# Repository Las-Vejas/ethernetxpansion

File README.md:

# ethernetxpansion

This is an ethernet adapter for the [Hackxpansion console](https://github.com/hackclub/hackxpansion). It uses the WIZnet W5500 chip and the Hanrun HR911105A ethernet plug.

<h2 align="center">Pictures</h2>

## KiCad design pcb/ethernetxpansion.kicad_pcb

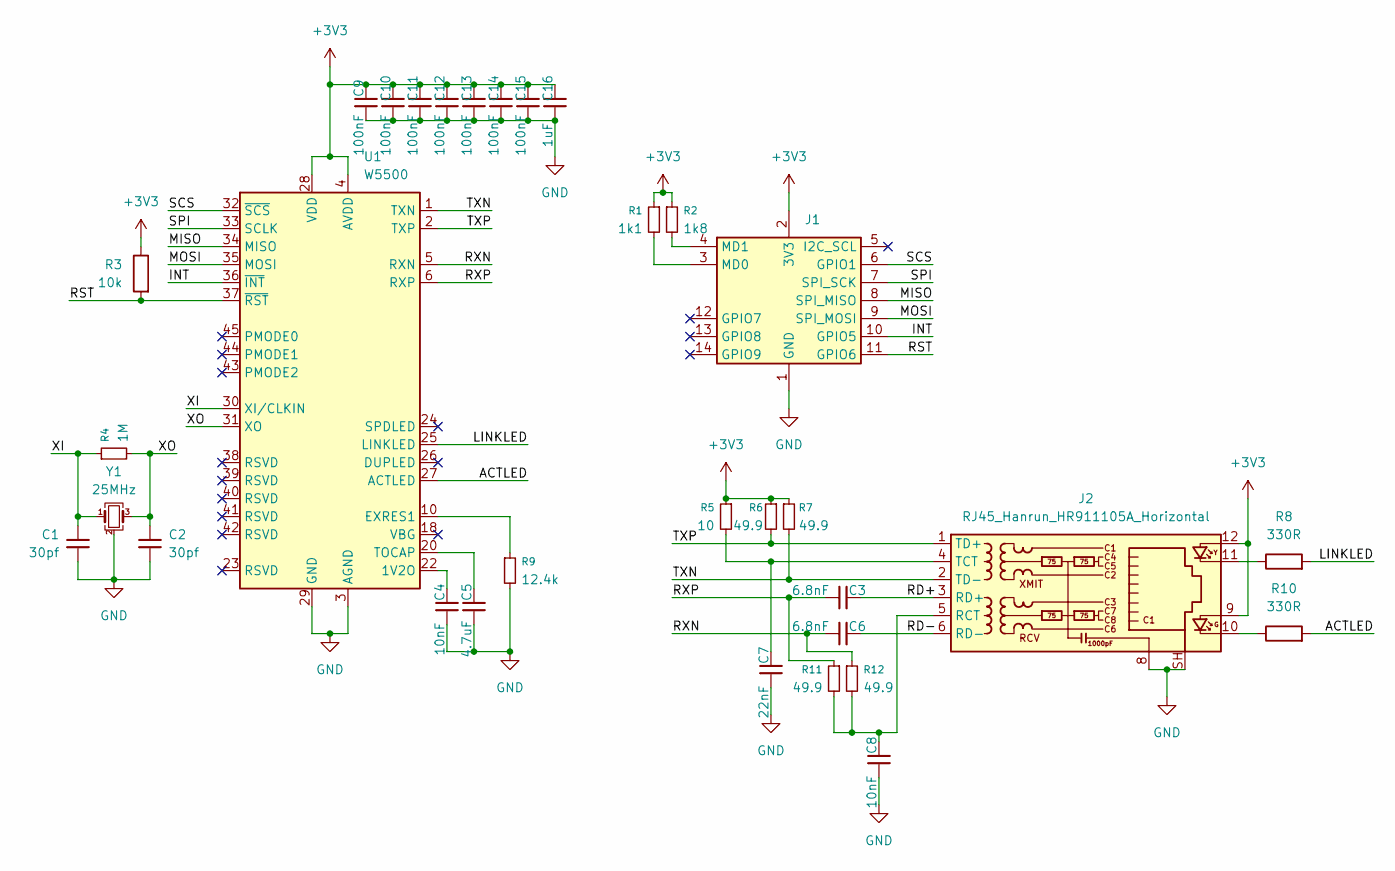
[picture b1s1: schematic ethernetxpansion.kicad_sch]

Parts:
C1, C2: 30pf; C_0402_1005Metric
C3, C6: 6.8nF; C_0402_1005Metric
C4, C8: 10nF; C_0402_1005Metric
C5: 4.7uF; C_0402_1005Metric
C7: 22nF; C_0402_1005Metric
C9, C10, C11, C12, C13, C14, C15: 100nF; C_0402_1005Metric
C16: 1uF; C_0402_1005Metric
J1: Male_Module
J2: RJ45_Hanrun_HR911105A_Horizontal
R1: 1k1; R_0402_1005Metric
R2: 1k8; R_0402_1005Metric
R3: 10k; R_0402_1005Metric
R4: 1M; R_0402_1005Metric
R5: 10; R_0402_1005Metric
R6, R7, R11, R12: 49.9; R_0402_1005Metric
R8, R10: 330R; R_0402_1005Metric
R9: 12.4k; R_0402_1005Metric
U1: W5500; LQFP-48_7x7mm_P0.5mm
Y1: 25MHz; Crystal_SMD_3225-4Pin_3.2x2.5mm

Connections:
+3V3: C9.2, C10.2, C11.2, C12.2, C13.2, C14.2, C15.2, C16.2, J1.2 (3V3), J2.9, J2.12, R1.1, R2.1, R3.1, R5.1, R6.1, R7.1, U1.4 (AVDD), U1.8 (AVDD), U1.11 (AVDD), U1.15 (AVDD), U1.17 (AVDD), U1.21 (AVDD), U1.28 (VDD)
/ACTLED: R10.2, U1.27 (ACTLED)
/INT: J1.10 (GPIO5), U1.36 (~INT)
/LINKLED: R8.2, U1.25 (LINKLED)
/MISO: J1.8 (SPI_MISO), U1.34 (MISO)
/MOSI: J1.9 (SPI_MOSI), U1.35 (MOSI)
/RD+: C3.2, J2.3 (RD+)
/RD-: C6.2, J2.6 (RD-)
/RST: J1.11 (GPIO6), R3.2, U1.37 (~RST)
/RXN: C6.1, R12.1, U1.5 (RXN)
/RXP: C3.1, R11.1, U1.6 (RXP)
/SCS: J1.6 (GPIO1), U1.32 (~SCS)
/SPI: J1.7 (SPI_SCK), U1.33 (SCLK)
/TXN: J2.2 (TD-), R7.2, U1.1 (TXN)
/TXP: J2.1 (TD+), R6.2, U1.2 (TXP)
/XI: C1.1, R4.1, U1.30 (XI/CLKIN), Y1.1
/XO: C2.1, R4.2, U1.31 (XO), Y1.3
GND: C1.2, C2.2, C4.1, C5.1, C7.1, C8.1, C9.1, C10.1, C11.1, C12.1, C13.1, C14.1, C15.1, C16.1, J1.1 (GND), J2.8, J2.SH, R9.2, U1.3 (AGND), U1.9 (AGND), U1.14 (AGND), U1.16 (AGND), U1.19 (AGND), U1.29 (GND), U1.48 (AGND), Y1.2 (G), Y1.4 (G)
unnamed: J1.3 (MD0), R1.2
unnamed: J1.4 (MD1), R2.2
unnamed: J2.10, R10.1
unnamed: J2.11, R8.1
unnamed: C8.2, J2.5 (RCT), R11.2, R12.2
unnamed: C7.2, J2.4 (TCT), R5.2
unnamed: C4.2, U1.22 (1V2O)
unnamed: R9.1, U1.10 (EXRES1)
unnamed: C5.2, U1.20 (TOCAP)

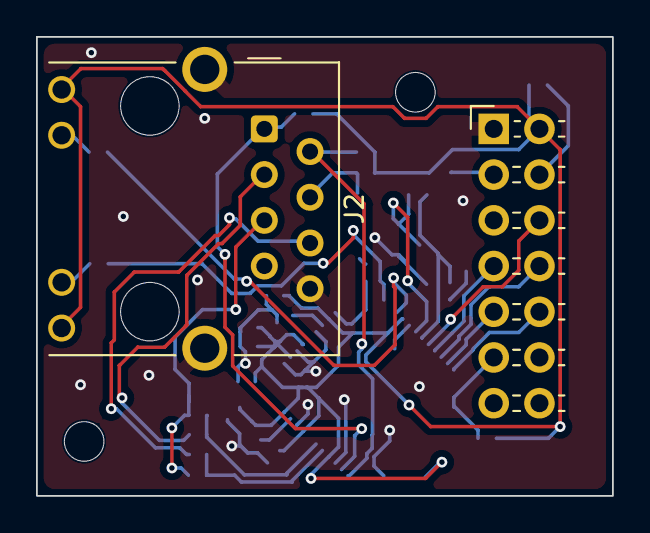
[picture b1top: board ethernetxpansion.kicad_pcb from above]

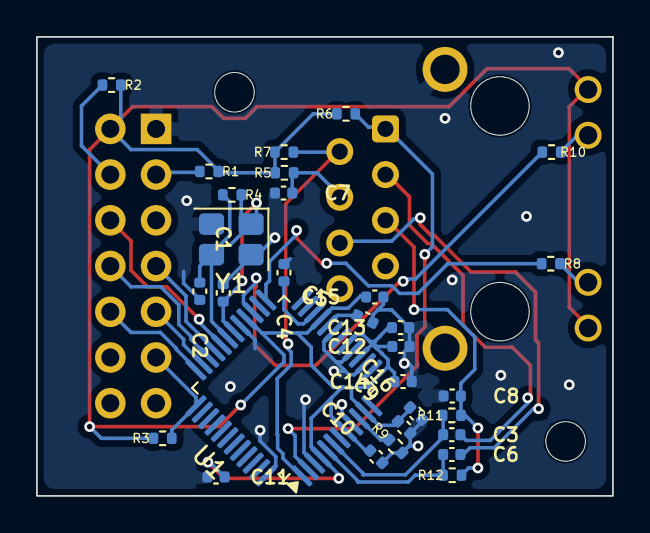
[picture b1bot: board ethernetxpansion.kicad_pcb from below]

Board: 4 copper layers, 32.0 x 25.5 mm, 32 parts (30 on the bottom side), 27 nets.
